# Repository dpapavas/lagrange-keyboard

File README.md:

# The Lagrange keyboard

The Lagrange is a configurable, split, handwired keyboard, designed
for ergonomics.  This is meant in the sense that as many keys as
possible should be accessible with the minimum possible effort,
although some less reachable keys are also incorporated in the design
as they can still be useful.  Features that attempt to improve
ergonomics include concave main sections, convex thumb sections, a
tenting stand, palm keys and specially designed keycap shapes.  To get
a better idea of what all this looks like, see the [3D model of the
final assembly](./things/right-assembly.stl) and the photos of my
build in the [doc/](./doc/) directory.

The Lagrange is of course inspired by the designs that preceded it,
most notably the [Dactyl](https://github.com/adereth/dactyl-keyboard)
and the [Dactyl-ManuForm](https://github.com/tshort/dactyl-keyboard).
Differences with these designs and additional contributions to the art
include:

* A new thumb section layout, based on the spherical workspace of the
  thumb (and with the added bonus of a cross-shaped set of keys,
  useful for "directional" functions).
* Palm keys, meant to be pressed with the edge of the palm, without
  needing to leave the home row.
* An integrated, configurable tenting stand.
* Non-standard keycap designs for thumb and palm keys.
* Code features aiding exploration of different configurations, such
  as "interference test builds", allowing design validation prior to
  printing and "partial test builds", allowing quick prints of
  arbitrary subsections of the keyboard.  (These features can be
  instrumental to ergonomics optimization, as they allow both deeper
  exploration of possible configurations and minimizing the key
  distances within a given configuration, while still avoiding
  interference between switches, keycaps and the case.)

A further goal of the design was to comprise parts, both mechanical
and electrical, that fit together and that can be easily assembled to
result in something that can withstand the wear and tear of daily use.

## Building a Lagrange

If you want to build your own Lagrange, you can find detailed
instructions in [BUILD.md](./BUILD.md).

## License

Copyright © 2020 Dimitris Papavasiliou

This program (which includes everything except the
[things/](./things/), [kicad/](./kicad/) and [doc/](./doc/)
directories, is distributed under the [GNU Affero General Public
License Version 3](./LICENSE.AGPL).  The controller PCB design
residing in [kicad/](./kicad/), is distributed under the [GNU General
Public License Version 3](./LICENSE.GPL). Finally, the generated
models residing in [things/](./things/), as well as the material in
[doc/](./doc/), are licensed under a [Creative Commons
Attribution-ShareAlike 4.0 International License](./LICENSE.CC).

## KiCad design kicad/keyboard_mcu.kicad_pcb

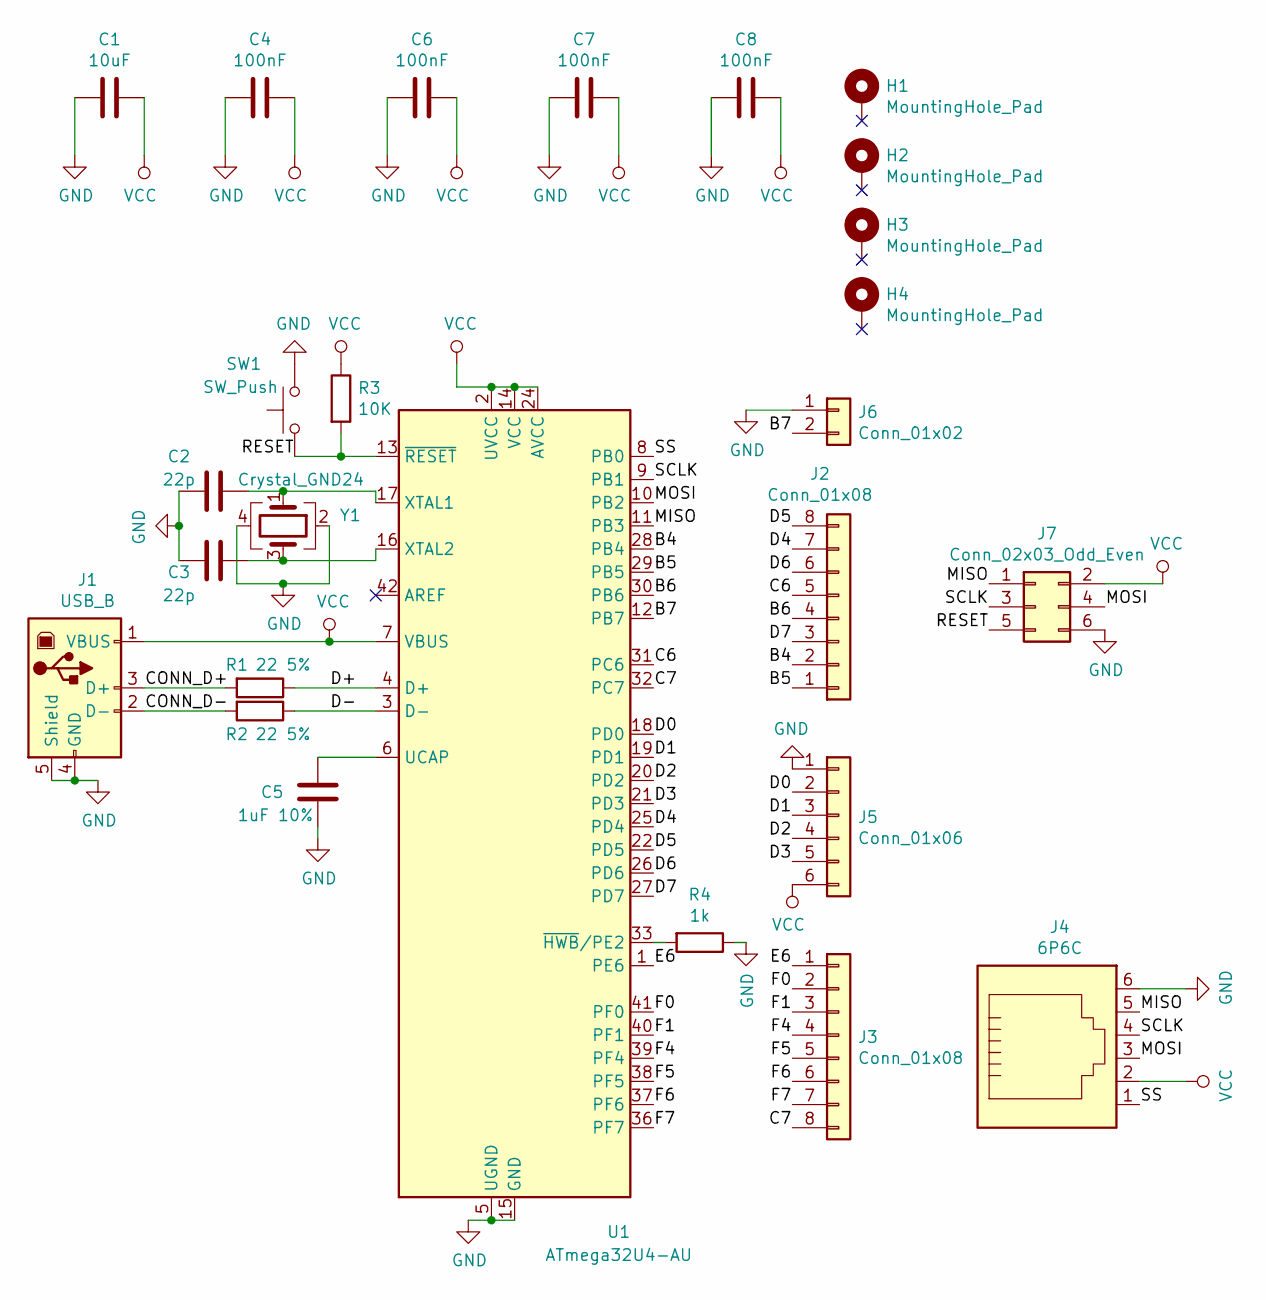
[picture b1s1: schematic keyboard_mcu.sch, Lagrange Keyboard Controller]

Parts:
C1: 10uF; C_0805_2012Metric_Pad1.15x1.40mm_HandSolder
C2, C3: 22p; C_0603_1608Metric_Pad1.05x0.95mm_HandSolder
C4, C6, C7, C8: 100nF; C_0603_1608Metric_Pad1.05x0.95mm_HandSolder
C5: 1uF 10%; C_0603_1608Metric_Pad1.05x0.95mm_HandSolder
H1, H2, H3, H4: MountingHole_Pad; MountingHole_3.2mm_M3_Pad
J1: USB_B; USB_B_TE_5787834_Vertical
J2, J3: Conn_01x08; JST_PH_B8B-PH-K_1x08_P2.00mm_Vertical
J4: 6P6C; RJ25_TE_5520425
J5: Conn_01x06; JST_PH_B6B-PH-K_1x06_P2.00mm_Vertical
J6: Conn_01x02; PinHeader_1x02_P2.54mm_Vertical
J7: Conn_02x03_Odd_Even; PinHeader_2x03_P2.54mm_Vertical
R1, R2: 22 5%; R_0603_1608Metric_Pad1.05x0.95mm_HandSolder
R3: 10K; R_0603_1608Metric_Pad1.05x0.95mm_HandSolder
R4: 1k; R_0603_1608Metric_Pad1.05x0.95mm_HandSolder
SW1: SW_Push; SW_SPST_TL3305B
U1: ATmega32U4-AU; TQFP-44_10x10mm_P0.8mm_Countoured
Y1: Crystal_GND24; Crystal_SMD_Abracon_ABM3B-4Pin_5.0x3.2mm_HandSoldering

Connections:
/B4: J2.2, U1.28 (PB4)
/B5: J2.1, U1.29 (PB5)
/B6: J2.4, U1.30 (PB6)
/B7: J6.2, U1.12 (PB7)
/C6: J2.5, U1.31 (PC6)
/C7: J3.8, U1.32 (PC7)
/CONN_D+: J1.3 (D+), R1.2
/CONN_D-: J1.2 (D-), R2.2
/D0: J5.2, U1.18 (PD0)
/D1: J5.3, U1.19 (PD1)
/D2: J5.4, U1.20 (PD2)
/D3: J5.5, U1.21 (PD3)
/D4: J2.7, U1.25 (PD4)
/D5: J2.8, U1.22 (PD5)
/D6: J2.6, U1.26 (PD6)
/D7: J2.3, U1.27 (PD7)
/D+: R1.1, U1.4 (D+)
/D-: R2.1, U1.3 (D-)
/E6: J3.1, U1.1 (PE6)
/F0: J3.2, U1.41 (PF0)
/F1: J3.3, U1.40 (PF1)
/F4: J3.4, U1.39 (PF4)
/F5: J3.5, U1.38 (PF5)
/F6: J3.6, U1.37 (PF6)
/F7: J3.7, U1.36 (PF7)
/MISO: J4.5, J7.1, U1.11 (PB3)
/MOSI: J4.3, J7.4, U1.10 (PB2)
/RESET: J7.5, R3.2, SW1.1, U1.13 (~RESET)
/SCLK: J4.4, J7.3, U1.9 (PB1)
/SS: J4.1, U1.8 (PB0)
GND: C1.2, C2.2, C3.2, C4.2, C5.2, C6.2, C7.2, C8.2, J1.4 (GND), J1.5 (Shield), J4.6, J5.1, J6.1, J7.6, R4.1, SW1.2, U1.5 (UGND), U1.15 (GND), U1.23 (GND), U1.35 (GND), U1.43 (GND), Y1.2, Y1.4
unnamed: C2.1, U1.17 (XTAL1), Y1.1
unnamed: C3.1, U1.16 (XTAL2), Y1.3
unnamed: C5.1, U1.6 (UCAP)
unnamed: R4.2, U1.33 (~HWB~/PE2)
VCC: C1.1, C4.1, C6.1, C7.1, C8.1, J1.1 (VBUS), J4.2, J5.6, J7.2, R3.1, U1.2 (UVCC), U1.7 (VBUS), U1.14 (VCC), U1.24 (AVCC), U1.34 (VCC), U1.44 (AVCC)

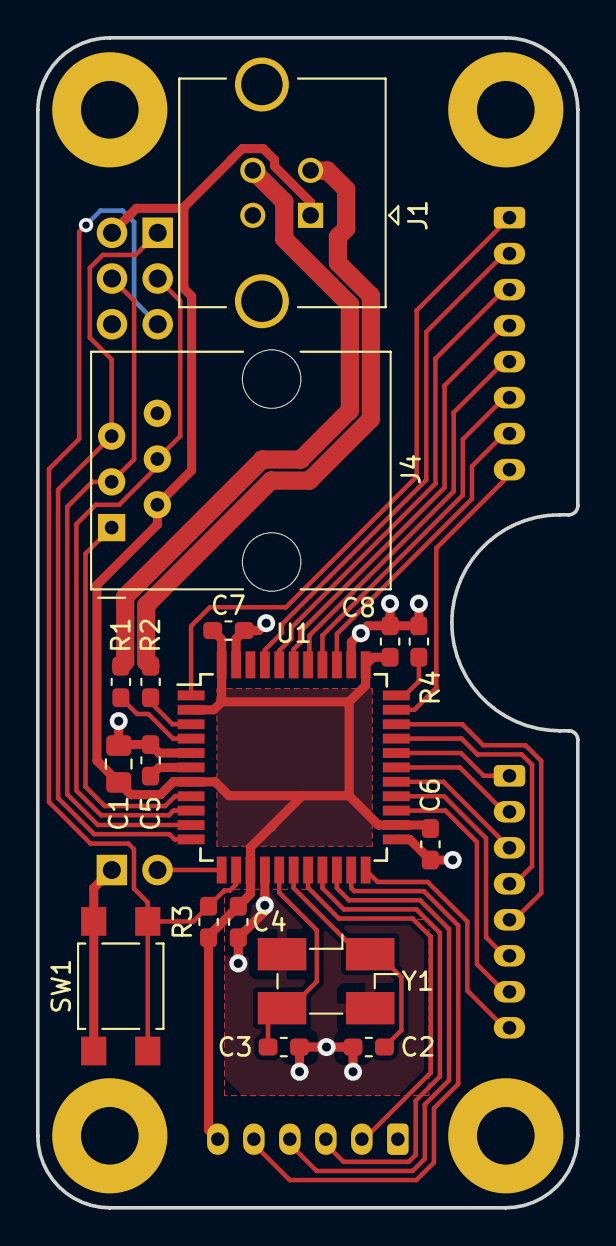
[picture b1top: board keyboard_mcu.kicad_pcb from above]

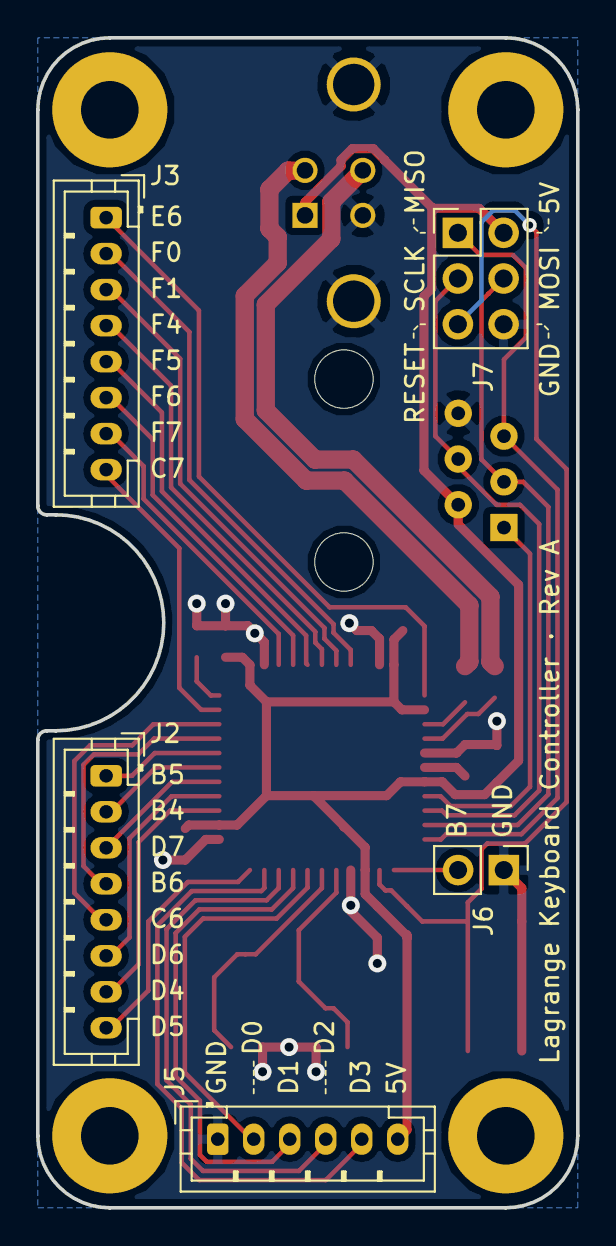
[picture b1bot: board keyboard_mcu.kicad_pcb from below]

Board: 2 copper layers, 30.0 x 65.0 mm, 26 parts (5 on the bottom side), 36 nets.

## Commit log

2020-12-30 Import sources, models and documentation.
2021-01-22 Add snapshot of design iterations.
2021-02-27 Add a section on required keycaps to the build guide.
2021-03-17 Add ibom
    Generated via https://github.com/openscopeproject/InteractiveHtmlBom
    This is useful for users who are unfamiliar with electrical
    engineering and KiCad.
2021-03-21 Add interactive BOM.
    Generated via https://github.com/openscopeproject/InteractiveHtmlBom
    This is useful for users who are unfamiliar with electrical
    engineering and KiCad.
2021-03-25 Improve documentation of fastening harware.
2021-04-24 Yes, I cut the middle pin :>
2021-05-04 Clarify text on cuttin PCB mount switch pins.
    Resolves #6
2021-05-07 Update documentation on QMK.
2021-05-19 Add the bridge.
2021-05-21 Update assembly STL file.
2021-06-01 Fix (most) non-manifold edges in the top part.
    Fixes #4
2021-11-02 Add cylindrical keycap family and keycap legends.
